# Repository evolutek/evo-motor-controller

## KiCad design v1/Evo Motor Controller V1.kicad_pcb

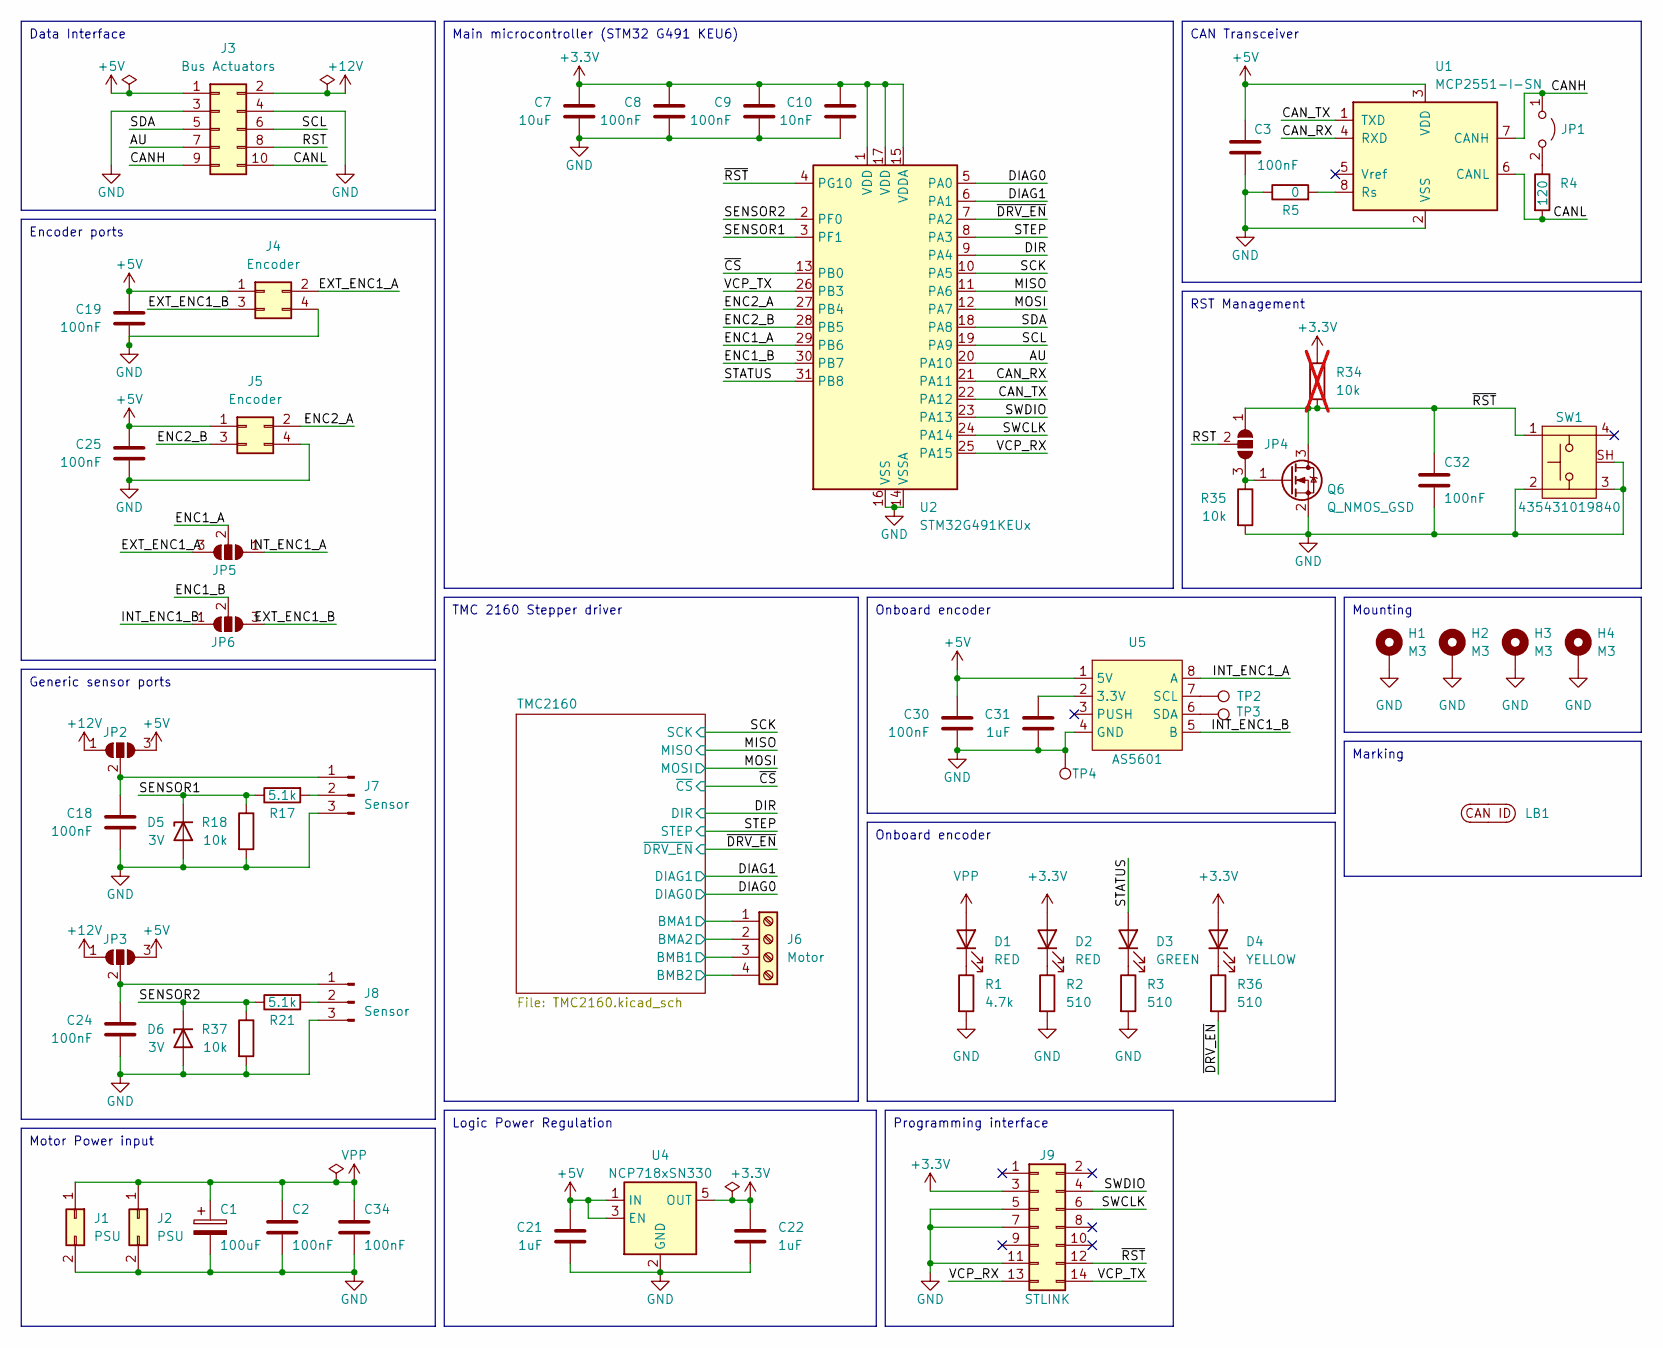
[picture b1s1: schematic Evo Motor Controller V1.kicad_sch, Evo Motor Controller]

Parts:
C1: 100uF; CP_Elec_6.3x7.7
C2, C3, C8, C9, C18, C19, C24, C25, C30, C32, C34: 100nF; C_0603_1608Metric
C7: 10uF; C_0603_1608Metric
C10: 10nF; C_0603_1608Metric
C21, C22, C31: 1uF; C_0603_1608Metric
D1, D2: RED; LED_0805_2012Metric
D3: GREEN; LED_0805_2012Metric
D4: YELLOW; LED_0805_2012Metric
D5, D6: 3V; D_SOD-523
H1, H2, H3, H4: M3; MountingHole_3.2mm_M3_Pad_Via
J1, J2: PSU; 66200221022
J3: Bus Actuators; 690367281076
J4, J5: Encoder; B04B-PASK
J6: Motor; PhoenixContact_MC_1,5_4-G-3.5_1x04_P3.50mm_Horizontal
J7, J8: Sensor; B03B-PASK
J9: STLINK; 62701420621
JP1: Jumper_2_Open; SolderJumper-2_P1.3mm_Open_RoundedPad1.0x1.5mm
JP2, JP3, JP4, JP5, JP6: SolderJumper_3_Open; SolderJumper-3_P1.3mm_Open_RoundedPad1.0x1.5mm
LB1: CAN ID Label 2
Q6: Q_NMOS_GSD; SOT-23
R1: 4.7k; R_0603_1608Metric
R2, R3, R36: 510; R_0603_1608Metric
R4: 120; R_0603_1608Metric
R5: 0; R_0603_1608Metric
R17, R21: 5.1k; R_0603_1608Metric
R18, R35, R37: 10k; R_0603_1608Metric
R34: 10k; R_0603_1608Metric; not fitted
SW1: 435431019840
TP2, TP3, TP4: TestPoint; TestPoint_Pad_D1.0mm
U1: MCP2551-I-SN; SOIC-8_3.9x4.9mm_P1.27mm
U2: STM32G491KEUx; QFN-32-1EP_5x5mm_P0.5mm_EP3.45x3.45mm-Without thermal pad
U4: NCP718xSN330; SOT-23-5
U5: AS5601; SOIC-8_3.9x4.9mm_P1.27mm

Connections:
+3.3V: C7.1, C8.1, C9.1, C10.1, C22.1, D2.2 (A), D4.2 (A), J9.3, R34.1, U2.1 (VDD), U2.15 (VDDA), U2.17 (VDD), U4.5 (OUT); also elsewhere on the board
+5V: C3.1, C19.1, C21.1, C25.1, C30.1, J3.1, J4.1, J5.1, JP2.3 (B), JP3.3 (B), U1.3 (VDD), U4.1 (IN), U4.3 (EN), U5.1 (5V)
+12V: J3.2, JP2.1 (A), JP3.1 (A); also elsewhere on the board
/AU: J3.7, U2.20 (PA10)
/CANH: J3.9, JP1.1 (A), U1.7 (CANH)
/CANL: J3.10, R4.2, U1.6 (CANL)
/CAN_RX: U1.4 (RXD), U2.21 (PA11)
/CAN_TX: U1.1 (TXD), U2.22 (PA12)
/DIAG0: U2.5 (PA0); also elsewhere on the board
/DIAG1: U2.6 (PA1); also elsewhere on the board
/DIR: U2.9 (PA4); also elsewhere on the board
/ENC1_A: JP5.2 (C), U2.29 (PB6)
/ENC1_B: JP6.2 (C), U2.30 (PB7)
/ENC2_A: J5.2, U2.27 (PB4)
/ENC2_B: J5.3, U2.28 (PB5)
/EXT_ENC1_A: J4.2, JP5.3 (B)
/EXT_ENC1_B: J4.3, JP6.3 (B)
/INT_ENC1_A: JP5.1 (A), U5.8 (A)
/INT_ENC1_B: JP6.1 (A), U5.5 (B)
/MISO: U2.11 (PA6); also elsewhere on the board
/MOSI: U2.12 (PA7); also elsewhere on the board
/RST: J3.8, JP4.2 (C)
/SCK: U2.10 (PA5); also elsewhere on the board
/SCL: J3.6, U2.19 (PA9)
/SDA: J3.5, U2.18 (PA8)
/SENSOR1: D5.1 (K), R17.1, R18.1, U2.3 (PF1)
/SENSOR2: D6.1 (K), R21.1, R37.1, U2.2 (PF0)
/STATUS: D3.2 (A), U2.31 (PB8)
/STEP: U2.8 (PA3); also elsewhere on the board
/SWCLK: J9.6, U2.24 (PA14)
/SWDIO: J9.4, U2.23 (PA13)
/TMC2160/BMA1: J6.1; also elsewhere on the board
/TMC2160/BMA2: J6.2; also elsewhere on the board
/TMC2160/BMB1: J6.3; also elsewhere on the board
/TMC2160/BMB2: J6.4; also elsewhere on the board
/VCP_RX: J9.13, U2.25 (PA15)
/VCP_TX: J9.14, U2.26 (PB3)
/~CS: U2.13 (PB0); also elsewhere on the board
/~DRV_EN: R36.2, U2.7 (PA2); also elsewhere on the board
/~RST: C32.1, J9.12, JP4.1 (A), Q6.3 (D), R34.2, SW1.1, U2.4 (PG10)
GND: C1.2, C2.2, C3.2, C7.2, C8.2, C9.2, C10.2, C18.2, C19.2, C21.2, C22.2, C24.2, C25.2, C30.2, C31.2, C32.2, C34.2, D5.2 (A), D6.2 (A), H1.1, H2.1, H3.1, H4.1, J1.2, J2.2, J3.3, J3.4, J4.4, J5.4, J7.3, J8.3, J9.5, J9.7, J9.11, Q6.2 (S), R1.2, R2.2, R3.2, R5.1, R18.2, R35.2, R37.2, SW1.2, SW1.3, SW1.SH, TP4.1, U1.2 (VSS), U2.14 (VSSA), U2.16 (VSS), U2.32 (VSS), U4.2 (GND), U5.4 (GND); also elsewhere on the board
unnamed: D1.1 (K), R1.1
unnamed: D2.1 (K), R2.1
unnamed: D3.1 (K), R3.1
unnamed: D4.1 (K), R36.1
unnamed: C18.1, J7.1, JP2.2 (C)
unnamed: J7.2, R17.2
unnamed: C24.1, J8.1, JP3.2 (C)
unnamed: J8.2, R21.2
unnamed: JP1.2 (B), R4.1
unnamed: JP4.3 (B), Q6.1 (G), R35.1
unnamed: R5.2, U1.8 (Rs)
unnamed: C31.1, U5.2 (3.3V)
unnamed: TP2.1, U5.7 (SCL)
unnamed: TP3.1, U5.6 (SDA)
VPP: C1.1, C2.1, C34.1, D1.2 (A), J1.1, J2.1; also elsewhere on the board

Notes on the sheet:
Marking
Motor Power input
Onboard encoder
Generic sensor ports
Programming interface
Mounting
Data Interface
Encoder ports
TMC 2160 Stepper driver
CAN Transceiver
Logic Power Regulation
Main microcontroller (STM32 G491 KEU6)
RST Management

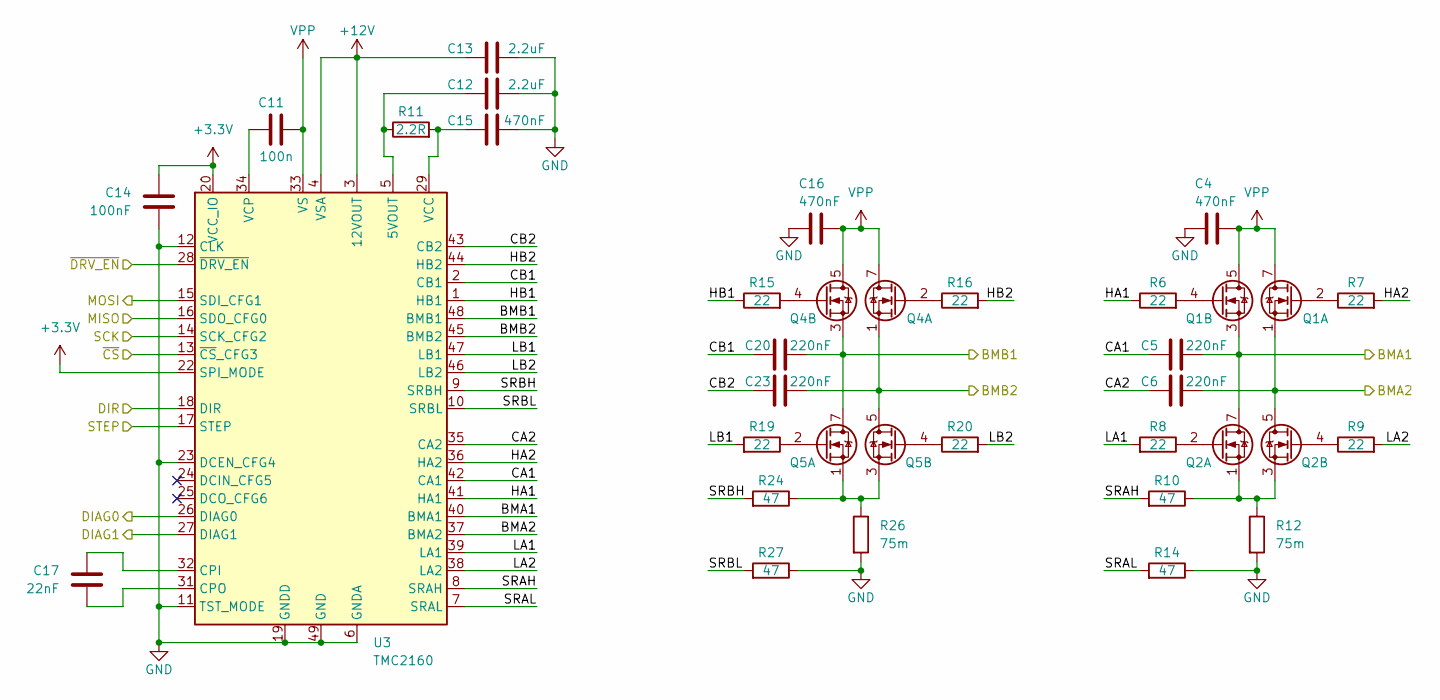
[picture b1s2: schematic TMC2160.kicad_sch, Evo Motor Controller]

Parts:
C4, C15, C16: 470nF; C_0603_1608Metric
C5, C6, C20, C23: 220nF; C_0603_1608Metric
C11: 100n; C_0603_1608Metric
C12, C13: 2.2uF; C_0603_1608Metric
C14: 100nF; C_0603_1608Metric
C17: 22nF; C_0603_1608Metric
Q1, Q2, Q4, Q5: Si9634DY; SO-8_3.9x4.9mm_P1.27mm
R6, R7, R8, R9, R15, R16, R19, R20: 22; R_0603_1608Metric
R10, R14, R24, R27: 47; R_0603_1608Metric
R11: 2.2R; R_0603_1608Metric
R12, R26: 75m; R_1206_3216Metric
U3: TMC2160; TQFP-48-1EP_7x7mm_P0.5mm_EP5x5mm

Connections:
+3.3V: C14.1, U3.20 (VCC_IO), U3.21 (VCC_IO), U3.22 (SPI_MODE); also elsewhere on the board
+12V: C13.1, U3.3 (12VOUT), U3.4 (VSA); also elsewhere on the board
/DIAG0: U3.26 (DIAG0); also elsewhere on the board
/DIAG1: U3.27 (DIAG1); also elsewhere on the board
/DIR: U3.18 (DIR); also elsewhere on the board
/MISO: U3.16 (SDO_CFG0); also elsewhere on the board
/MOSI: U3.15 (SDI_CFG1); also elsewhere on the board
/SCK: U3.14 (SCK_CFG2); also elsewhere on the board
/STEP: U3.17 (STEP); also elsewhere on the board
/TMC2160/BMA1: C5.1, Q1.3 (S), Q2.7 (D), Q2.8 (D), U3.40 (BMA1); also elsewhere on the board
/TMC2160/BMA2: C6.1, Q1.1 (S), Q2.5 (D), Q2.6 (D), U3.37 (BMA2); also elsewhere on the board
/TMC2160/BMB1: C20.1, Q4.3 (S), Q5.7 (D), Q5.8 (D), U3.48 (BMB1); also elsewhere on the board
/TMC2160/BMB2: C23.1, Q4.1 (S), Q5.5 (D), Q5.6 (D), U3.45 (BMB2); also elsewhere on the board
/TMC2160/CA1: C5.2, U3.42 (CA1)
/TMC2160/CA2: C6.2, U3.35 (CA2)
/TMC2160/CB1: C20.2, U3.2 (CB1)
/TMC2160/CB2: C23.2, U3.43 (CB2)
/TMC2160/HA1: R6.1, U3.41 (HA1)
/TMC2160/HA2: R7.2, U3.36 (HA2)
/TMC2160/HB1: R15.1, U3.1 (HB1)
/TMC2160/HB2: R16.2, U3.44 (HB2)
/TMC2160/LA1: R8.2, U3.39 (LA1)
/TMC2160/LA2: R9.2, U3.38 (LA2)
/TMC2160/LB1: R19.2, U3.47 (LB1)
/TMC2160/LB2: R20.2, U3.46 (LB2)
/TMC2160/SRAH: R10.2, U3.8 (SRAH)
/TMC2160/SRAL: R14.2, U3.7 (SRAL)
/TMC2160/SRBH: R24.2, U3.9 (SRBH)
/TMC2160/SRBL: R27.2, U3.10 (SRBL)
/~CS: U3.13 (~CS_CFG3); also elsewhere on the board
/~DRV_EN: U3.28 (~DRV_EN); also elsewhere on the board
GND: C4.2, C12.2, C13.2, C14.2, C15.2, C16.2, R12.2, R14.1, R26.2, R27.1, U3.6 (GNDA), U3.11 (TST_MODE), U3.12 (CLK), U3.19 (GNDD), U3.23 (DCEN_CFG4), U3.30 (GNDD), U3.49 (GND); also elsewhere on the board
unnamed: Q1.2 (G), R7.1
unnamed: Q1.4 (G), R6.2
unnamed: Q2.2 (G), R8.1
unnamed: Q2.1 (S), Q2.3 (S), R10.1, R12.1
unnamed: Q2.4 (G), R9.1
unnamed: Q4.2 (G), R16.1
unnamed: Q4.4 (G), R15.2
unnamed: Q5.2 (G), R19.1
unnamed: Q5.1 (S), Q5.3 (S), R24.1, R26.1
unnamed: Q5.4 (G), R20.1
unnamed: C12.1, R11.1, U3.5 (5VOUT)
unnamed: C17.1, U3.32 (CPI)
unnamed: C17.2, U3.31 (CPO)
unnamed: C15.1, R11.2, U3.29 (VCC)
unnamed: C11.1, U3.34 (VCP)
VPP: C4.1, C11.2, C16.1, Q1.5 (D), Q1.6 (D), Q1.7 (D), Q1.8 (D), Q4.5 (D), Q4.6 (D), Q4.7 (D), Q4.8 (D), U3.33 (VS); also elsewhere on the board

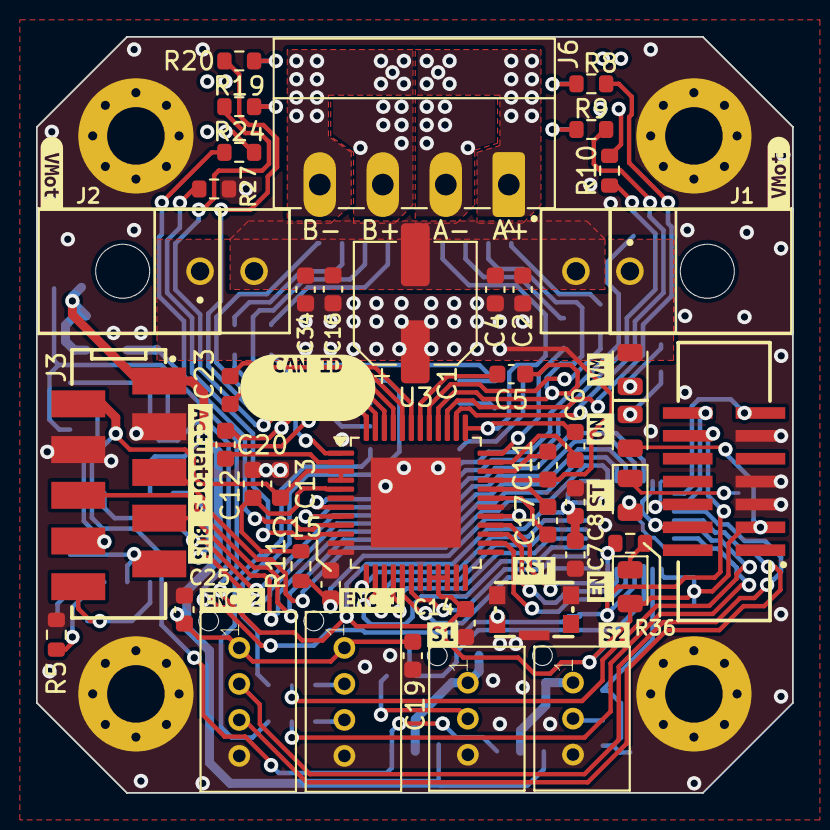
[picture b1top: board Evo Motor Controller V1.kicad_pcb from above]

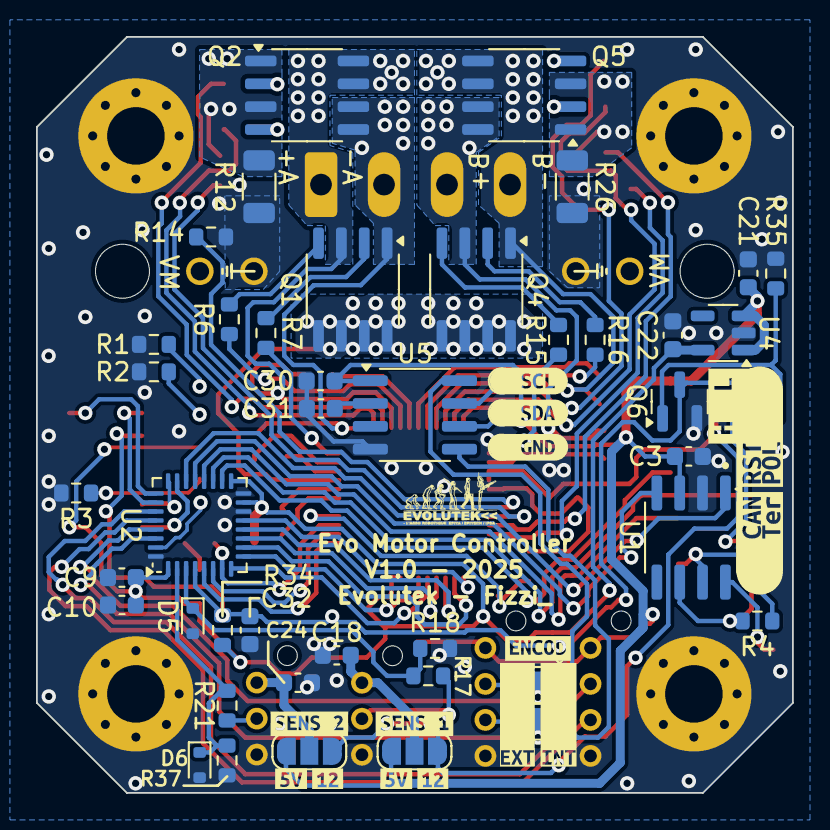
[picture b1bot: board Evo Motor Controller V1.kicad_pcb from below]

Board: 2 copper layers, 42.0 x 42.0 mm, 123 parts (62 on the bottom side), 87 nets.

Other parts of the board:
kibuzzard-676B4A85: G***; kibuzzard-676B4A85
kibuzzard-676B4AC4: G***; kibuzzard-676B4AC4
kibuzzard-676B4BE4: G***; kibuzzard-676B4BE4
kibuzzard-676B4093: G***; kibuzzard-676B4093
kibuzzard-676F6C1C: G***; kibuzzard-676F6C1C
kibuzzard-676F6C2F: G***; kibuzzard-676F6C2F
kibuzzard-67856E2C: G***; kibuzzard-67856E2C
kibuzzard-67856E49: G***; kibuzzard-67856E49
kibuzzard-67856FF7, kibuzzard-67856FF7#2: G***; kibuzzard-67856FF7
kibuzzard-678570A8: G***; kibuzzard-678570A8
kibuzzard-678570B0: G***; kibuzzard-678570B0
kibuzzard-678570B4: G***; kibuzzard-678570B4
kibuzzard-678572E9: G***; kibuzzard-678572E9
kibuzzard-6786847E: G***; kibuzzard-6786847E
kibuzzard-6786849F: G***; kibuzzard-6786849F
kibuzzard-6786851A: G***; kibuzzard-6786851A
kibuzzard-67857003, kibuzzard-67857003#2: G***; kibuzzard-67857003
kibuzzard-67857028: G***; kibuzzard-67857028
kibuzzard-67857113: G***; kibuzzard-67857113
kibuzzard-67857122: G***; kibuzzard-67857122
kibuzzard-67857138: G***; kibuzzard-67857138
kibuzzard-67857263: G***; kibuzzard-67857263
kibuzzard-67857283: G***; kibuzzard-67857283
kibuzzard-67868504: G***; kibuzzard-67868504
kibuzzard-67868567: G***; kibuzzard-67868567

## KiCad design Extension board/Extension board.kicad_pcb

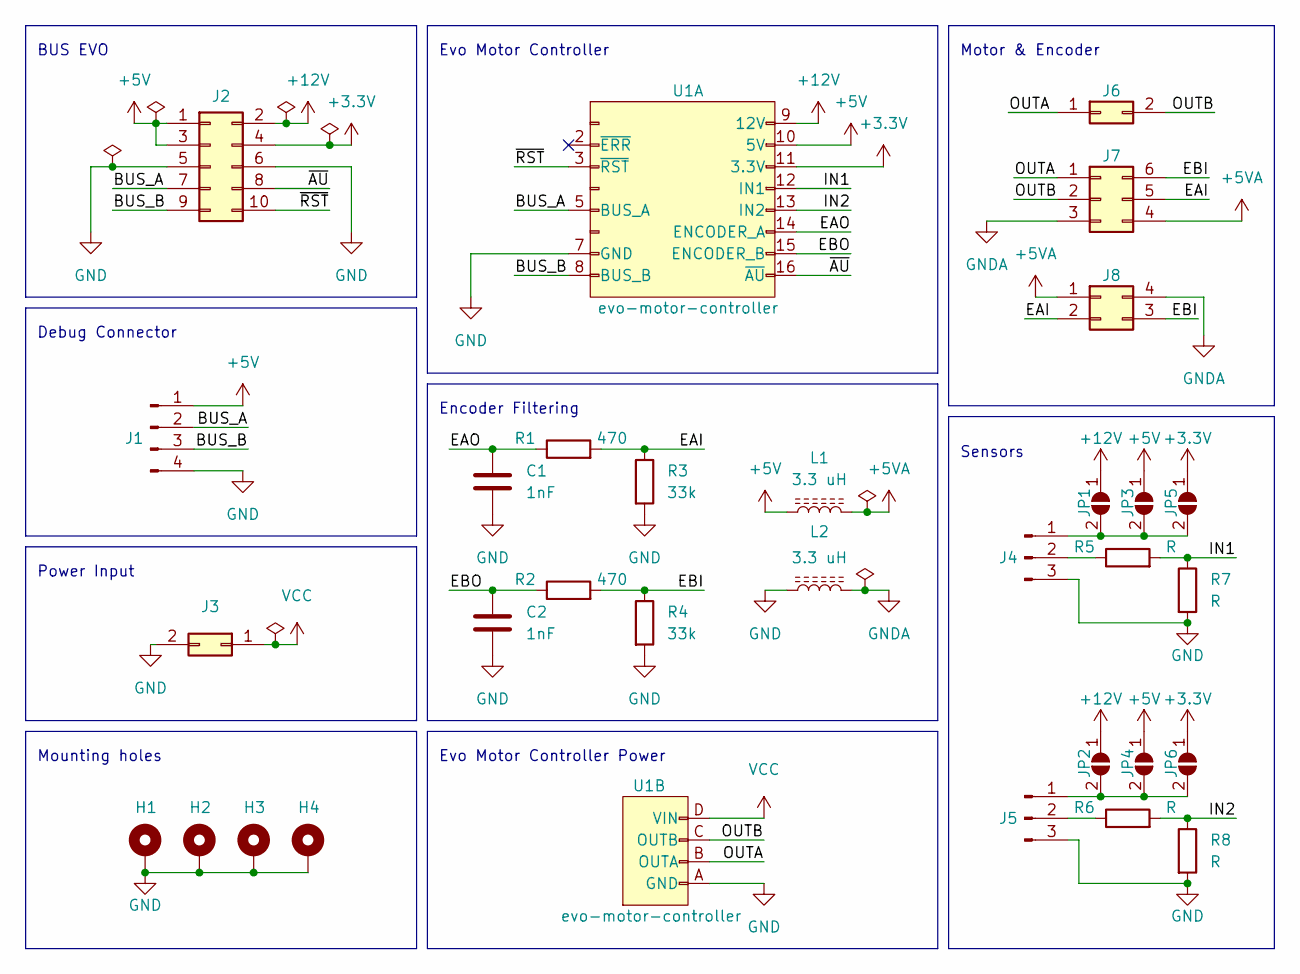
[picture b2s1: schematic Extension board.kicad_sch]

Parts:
C1, C2: 1nF; C_0603_1608Metric
H1, H2, H3, H4: MountingHole_Pad; MountingHole_3.2mm_M3_Pad_Via
J1: Conn_01x04_Male; B04B-PASK
J2: Conn_02x05_Odd_Even; 690367281076
J3, J6: Conn_02x01; 649002227222
J4, J5: Conn_01x03_Male; B03B-PASK
J7: Conn_02x03_Counter_Clockwise; 66200621022
J8: Conn_02x02_Counter_Clockwise; 66200421022
JP1, JP2, JP3, JP4, JP5, JP6: SolderJumper_2_Open; SolderJumper-2_P1.3mm_Open_TrianglePad1.0x1.5mm
L1, L2: 3.3 uH; L_0603_1608Metric
R1, R2: 470; R_0603_1608Metric
R3, R4: 33k; R_0603_1608Metric
R5, R6, R7, R8: R; R_0603_1608Metric
U1: evo-motor-controller

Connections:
+3.3V: J2.4, JP5.1 (A), JP6.1 (A), U1.11 (3.3V)
+5V: J1.1, J2.1, J2.3, JP3.1 (A), JP4.1 (A), L1.1, U1.10 (5V)
+5VA: J7.4, J8.1, L1.2
+12V: J2.2, JP1.1 (A), JP2.1 (A), U1.9 (12V)
/BUS_A: J1.2, J2.7, U1.5 (BUS_A)
/BUS_B: J1.3, J2.9, U1.8 (BUS_B)
/EAI: J7.5, J8.2, R1.2, R3.1
/EAO: C1.1, R1.1, U1.14 (ENCODER_A)
/EBI: J7.6, J8.3, R2.2, R4.1
/EBO: C2.1, R2.1, U1.15 (ENCODER_B)
/IN1: R5.2, R7.1, U1.12 (IN1)
/IN2: R6.2, R8.1, U1.13 (IN2)
/OUTA: J6.1, J7.1, U1.B (OUTA)
/OUTB: J6.2, J7.2, U1.C (OUTB)
/~AU: J2.8, U1.16 (~AU)
/~RST: J2.10, U1.3 (~RST)
GND: C1.2, C2.2, H1.1, H2.1, H3.1, H4.1, J1.4, J2.5, J2.6, J3.2, J4.3, J5.3, L2.1, R3.2, R4.2, R7.2, R8.2, U1.7 (GND), U1.A (GND)
GNDA: J7.3, J8.4, L2.2
unnamed: J4.1, JP1.2 (B), JP3.2 (B), JP5.2 (B)
unnamed: J4.2, R5.1
unnamed: J5.1, JP2.2 (B), JP4.2 (B), JP6.2 (B)
unnamed: J5.2, R6.1
VCC: J3.1, U1.D (VIN)

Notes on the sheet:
Evo Motor Controller
Encoder Filtering
Evo Motor Controller Power
Power Input
Motor & Encoder
Mounting holes
BUS EVO
Debug Connector
Sensors

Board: 2 copper layers, 31 parts (0 on the bottom side), 23 nets, no tracks yet.

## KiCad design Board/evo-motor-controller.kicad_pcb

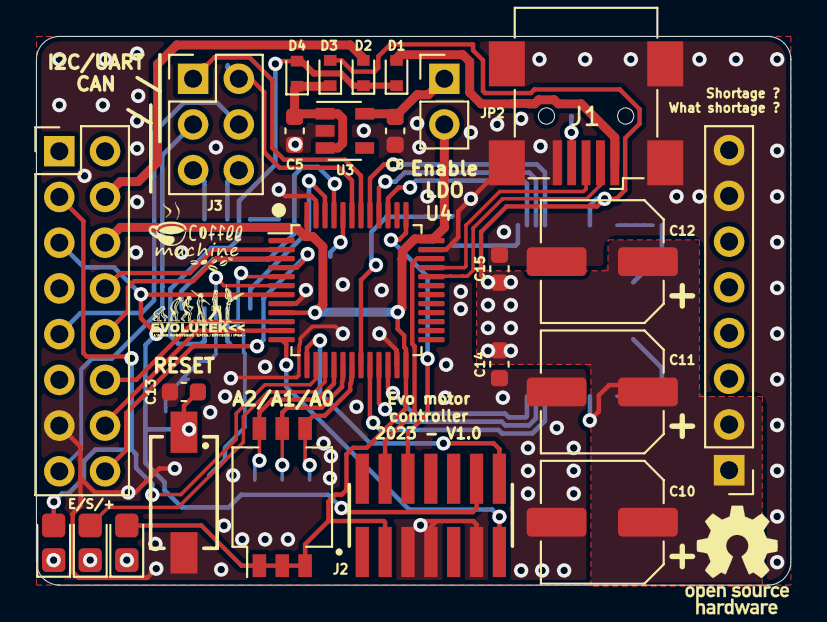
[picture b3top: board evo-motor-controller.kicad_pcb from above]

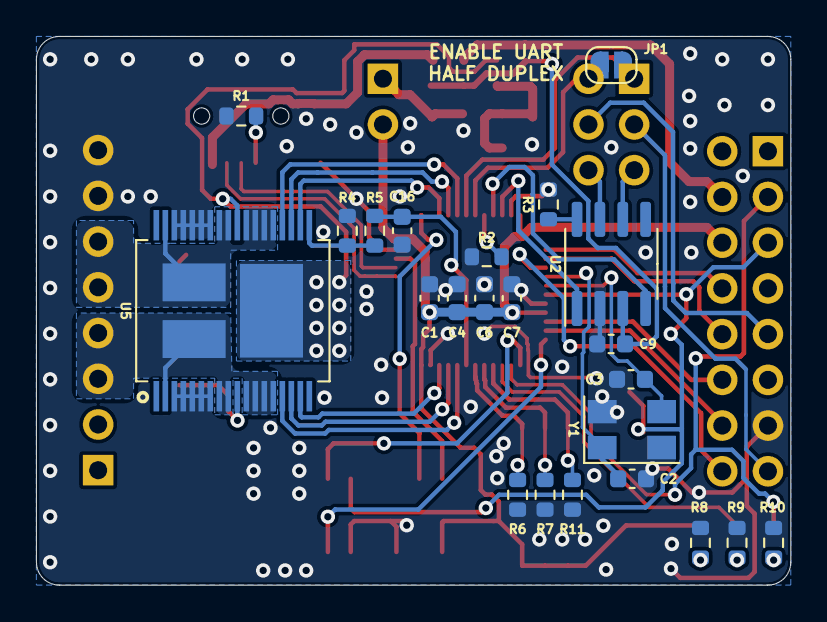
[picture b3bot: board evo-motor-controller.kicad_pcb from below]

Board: 2 copper layers, 41.9 x 30.5 mm, 47 parts (23 on the bottom side), 51 nets.

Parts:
C1, C14: 10uF; C_0603_1608Metric
C2, C3: 18pF; C_0603_1608Metric
C4, C6, C9, C13, C15: 100nF; C_0603_1608Metric
C5, C8: 1uF; C_0603_1608Metric
C7: 10nF; C_0603_1608Metric
C10, C11, C12: 100uF; C_Elec_6.3x7.7
C16: 33nF; C_0603_1608Metric
D1, D2, D3, D4: D; D_SOD-523
D5, D7: RED; LED_0805_2012Metric_Castellated
D6: YELLOW; LED_0805_2012Metric_Castellated
J1: USB_B_Mini; USB_Mini-B_Wuerth_65100516121_Horizontal
J2: FTSH-107-01-L-DV-K; SAMTEC_FTSH-107-01-L-DV-K
J3: Conn_02x03_Odd_Even; PinHeader_2x03_P2.54mm_Vertical
JP1: Jumper_NO_Small; SolderJumper-2_P1.3mm_Open_RoundedPad1.0x1.5mm
JP2: Jumper_NO_Small; PinHeader_1x02_P2.54mm_Vertical
R1: 100K; R_0603_1608Metric
R2, R3, R6, R7, R11: 10K; R_0603_1608Metric
R4, R5, R8, R9, R10: 1K; R_0603_1608Metric
SW1: SW_Push; 434121043836
SW2: SW_DIP_x03; SW_DIP_SPSTx03_Slide_KingTek_DSHP03TS_W7.62mm_P1.27mm
U1: G2-Port_extended; G2-port-extended
U2: MCP2551-I-SN; SOIC-8_3.9x4.9mm_P1.27mm
U3: NCP718xSN330; SOT-23-5
U4: STM32F103C8Tx; LQFP-48_7x7mm_P0.5mm
U5: VNH7040AYTR
Y1: 16 MHz; Crystal_SMD_5032-4Pin_5.0x3.2mm

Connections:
+3V3: C1.1, C4.1, C6.1, C7.1, D5.2, J2.3, JP2.2, SW2.1, SW2.2, SW2.3, U1.11, U4.9, U4.24, U4.36, U4.48
+5V: C9.1, D1.1, D2.1, D4.2, U2.3
/A0: R6.1, SW2.4, U4.18
/A1: R7.1, SW2.5, U4.17
/A2: R11.1, SW2.6, U4.16
/BUS_A: J3.4, U1.5
/BUS_B: J3.3, U1.8
/CANH: J3.6, U2.7
/CANL: J3.5, U2.6
/CAN_RX: U2.4, U4.45
/CAN_TX: U2.1, U4.46
/ENCODER_A: U1.14, U4.10
/ENCODER_B: U1.15, U4.11
/ERR_MOTOR: D7.2, U1.2, U4.14
/IN1: U1.12, U4.2
/IN2: U1.13, U4.3
/INA: U4.21, U5.3
/INB: U4.40, U5.4
/LED_STATUS: D6.2, U4.15
/MS: C16.1, R5.1, U4.19
/MS_EN: U4.39, U5.8
/OUTA: U1.C, U5.11
/OUTB: U1.B, U5.12
/PWM: U4.22, U5.5
/SCL-TX: J3.1, JP1.1, U4.42
/SDA-RX: J3.2, JP1.2, U4.43
/SEL0: U4.20, U5.6
/SEL1: U4.41, U5.7
/SWCLK: J2.6, U4.37
/SWDIO: J2.4, U4.34
/USB+: J1.3, U4.33
/USB-: J1.2, U4.32
/VCP_RX: J2.14, U4.13
/VCP_TX: J2.13, U4.12
/~AU: U1.16, U4.4
/~RST: C13.1, J2.12, SW1.1, U1.3, U4.7
GND: C1.2, C2.1, C3.1, C4.2, C5.2, C6.2, C7.2, C8.2, C9.2, C10.2, C11.2, C12.2, C13.2, C14.2, C15.2, C16.2, J1.5, J1.6, J2.5, J2.7, J2.11, R1.1, R2.1, R3.2, R4.2, R6.2, R7.2, R8.2, R9.2, R10.2, R11.2, SW1.2, U1.7, U1.A, U2.2, U3.2, U4.8, U4.23, U4.35, U4.47, U5.2, Y1.2, Y1.4
unnamed: C2.2, U4.5, Y1.1
unnamed: C3.2, U4.6, Y1.3
unnamed: C5.1, D3.1, D4.1, U3.1, U3.3
unnamed: C8.1, JP2.1, U3.5
unnamed: D1.2, J1.1
unnamed: D2.2, U1.10
unnamed: D5.1, R8.1
unnamed: D6.1, R9.1
unnamed: D7.1, R10.1
unnamed: J1.4, R1.2
unnamed: R2.2, U4.44
unnamed: R3.1, U2.8
unnamed: R4.1, R5.2, U5.9
VCC: C10.1, C11.1, C12.1, C14.1, C15.1, D3.2, U1.D, U5.1

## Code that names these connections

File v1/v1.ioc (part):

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Mcu.Name=STM32G491K(C-E)Ux
Mcu.Package=UFQFPN32
Mcu.UserName=STM32G491KEUx
PA0.GPIOParameters=GPIO_Label
PA0.GPIO_Label=DIAG0
PA0.Signal=GPXTI0
PA1.GPIOParameters=GPIO_Label
PA1.GPIO_Label=DIAG1
PA1.Signal=GPXTI1
PA10.GPIOParameters=GPIO_Label
PA10.GPIO_Label=AU
PA10.Signal=GPIO_Output
PA11.GPIOParameters=GPIO_Label
PA11.GPIO_Label=CAN_RX
PA11.Mode=FDCAN_Activate
PA11.Signal=FDCAN1_RX
PA12.GPIOParameters=GPIO_Label
PA12.GPIO_Label=CAN_TX
PA12.Mode=FDCAN_Activate
PA12.Signal=FDCAN1_TX
PA13.GPIOParameters=GPIO_Label
PA13.GPIO_Label=SWDIO
PA13.Mode=Serial_Wire
PA13.Signal=SYS_JTMS-SWDIO
PA14.GPIOParameters=GPIO_Label
PA14.GPIO_Label=SWCLK
PA14.Mode=Serial_Wire
PA14.Signal=SYS_JTCK-SWCLK
PA15.GPIOParameters=GPIO_Label
PA15.GPIO_Label=VCP_RX
PA15.Mode=Asynchronous
PA15.Signal=USART2_RX
PA2.GPIOParameters=GPIO_Label
PA2.GPIO_Label=N_EN
PA2.Signal=GPIO_Output
PA3.GPIOParameters=GPIO_Label
PA3.GPIO_Label=STEP
PA3.Signal=S_TIM2_CH4
PA4.GPIOParameters=GPIO_Label
PA4.GPIO_Label=DIR
PA4.Signal=GPIO_Output
PA5.GPIOParameters=GPIO_Label
PA5.GPIO_Label=SCK
PA5.Mode=Full_Duplex_Master
PA5.Signal=SPI1_SCK
PA6.GPIOParameters=GPIO_Label
PA6.GPIO_Label=MISO
PA6.Mode=Full_Duplex_Master
PA6.Signal=SPI1_MISO
PA7.GPIOParameters=GPIO_Label
PA7.GPIO_Label=MOSI
PA7.Mode=Full_Duplex_Master
PA7.Signal=SPI1_MOSI
PA8.GPIOParameters=GPIO_Label
PA8.GPIO_Label=SDA
PA8.Mode=I2C
PA8.Signal=I2C2_SDA
PA9.GPIOParameters=GPIO_Label
PA9.GPIO_Label=SCL
PA9.Mode=I2C
PA9.Signal=I2C2_SCL
PB0.GPIOParameters=GPIO_Label
PB0.GPIO_Label=N_CS
PB0.Signal=GPIO_Output
PB3.GPIOParameters=GPIO_Label
PB3.GPIO_Label=VCP_TX
PB3.Mode=Asynchronous
PB3.Signal=USART2_TX
PB4.GPIOParameters=GPIO_Label
PB4.GPIO_Label=ENC2_A
PB4.Signal=S_TIM3_CH1
PB5.GPIOParameters=GPIO_Label
PB5.GPIO_Label=ENC2_B
PB5.Signal=S_TIM3_CH2
PB6.GPIOParameters=GPIO_Label
PB6.GPIO_Label=ENC1_A
PB6.Signal=S_TIM4_CH1
PB7.GPIOParameters=GPIO_Label
PB7.GPIO_Label=ENC1_B
PB7.Signal=S_TIM4_CH2
PB8-BOOT0.GPIOParameters=GPIO_Label
PB8-BOOT0.GPIO_Label=STATUS
PB8-BOOT0.Signal=GPIO_Output
PF0-OSC_IN.GPIOParameters=GPIO_Label
PF0-OSC_IN.GPIO_Label=SENSOR_2
PF0-OSC_IN.Mode=IN10-Single-Ended
PF0-OSC_IN.Signal=ADC1_IN10
PF1-OSC_OUT.GPIOParameters=GPIO_Label
PF1-OSC_OUT.GPIO_Label=SENSOR_1
PF1-OSC_OUT.Mode=IN10-Single-Ended
PF1-OSC_OUT.Signal=ADC2_IN10
RCC.HSE_VALUE=8000000
RCC.SYSCLKFreq_VALUE=16000000
board=custom

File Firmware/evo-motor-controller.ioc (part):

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Mcu.Name=STM32F103C(8-B)Tx
Mcu.Package=LQFP48
Mcu.UserName=STM32F103C8Tx
PA0-WKUP.GPIOParameters=GPIO_Label
PA0-WKUP.GPIO_Label=ENCODER_A
PA0-WKUP.Signal=S_TIM2_CH1_ETR
PA1.GPIOParameters=GPIO_Label
PA1.GPIO_Label=ENCODER_B
PA1.Signal=S_TIM2_CH2
PA11.Mode=Device
PA11.Signal=USB_DM
PA12.Mode=Device
PA12.Signal=USB_DP
PA13.GPIOParameters=GPIO_Label
PA13.GPIO_Label=SWDIO
PA13.Mode=Serial_Wire
PA13.Signal=SYS_JTMS-SWDIO
PA14.GPIOParameters=GPIO_Label
PA14.GPIO_Label=SWCLK
PA14.Mode=Serial_Wire
PA14.Signal=SYS_JTCK-SWCLK
PA2.GPIOParameters=GPIO_Label
PA2.GPIO_Label=VCP_TX
PA2.Mode=Asynchronous
PA2.Signal=USART2_TX
PA3.GPIOParameters=GPIO_Label
PA3.GPIO_Label=VCP_RX
PA3.Mode=Asynchronous
PA3.Signal=USART2_RX
PA4.GPIOParameters=GPIO_Label
PA4.GPIO_Label=ERR_MOTOR
PA4.Signal=GPIO_Output
PA5.GPIOParameters=GPIO_Label
PA5.GPIO_Label=LED_STATUS
PA5.Signal=GPIO_Output
PB6.GPIOParameters=GPIO_Label
PB6.GPIO_Label=SCL
PB6.Mode=I2C
PB6.Signal=I2C1_SCL
PB7.GPIOParameters=GPIO_Label
PB7.GPIO_Label=SDA
PB7.Mode=I2C
PB7.Signal=I2C1_SDA
PB8.Mode=CAN_Activate
PB8.Signal=CAN_RX
PB9.Mode=CAN_Activate
PB9.Signal=CAN_TX
PC13-TAMPER-RTC.GPIOParameters=GPIO_Label
PC13-TAMPER-RTC.GPIO_Label=IN1
PC13-TAMPER-RTC.Signal=GPIO_Input
PC14-OSC32_IN.GPIOParameters=GPIO_Label
PC14-OSC32_IN.GPIO_Label=IN2
PC14-OSC32_IN.Signal=GPIO_Input
PC15-OSC32_OUT.GPIOParameters=GPIO_Label
PC15-OSC32_OUT.GPIO_Label=AU
PC15-OSC32_OUT.Signal=GPIO_Input
PD0-OSC_IN.Mode=HSE-External-Oscillator
PD0-OSC_IN.Signal=RCC_OSC_IN
PD1-OSC_OUT.Mode=HSE-External-Oscillator
PD1-OSC_OUT.Signal=RCC_OSC_OUT
RCC.HSEDivPLL=RCC_HSE_PREDIV_DIV2
RCC.HSE_VALUE=16000000
RCC.SYSCLKFreq_VALUE=72000000
RCC.SYSCLKSource=RCC_SYSCLKSOURCE_PLLCLK
board=custom

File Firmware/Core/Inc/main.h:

/* USER CODE BEGIN Header */
/**
  ******************************************************************************
  * @file           : main.h
  * @brief          : Header for main.c file.
  *                   This file contains the common defines of the application.
  ******************************************************************************
  * @attention
  *
  * <h2><center>&copy; Copyright (c) 2022 STMicroelectronics.
  * All rights reserved.</center></h2>
  *
  * This software component is licensed by ST under BSD 3-Clause license,
  * the "License"; You may not use this file except in compliance with the
  * License. You may obtain a copy of the License at:
  *                        opensource.org/licenses/BSD-3-Clause
  *
  ******************************************************************************
  */
/* USER CODE END Header */

/* Define to prevent recursive inclusion -------------------------------------*/
#ifndef __MAIN_H
#define __MAIN_H

#ifdef __cplusplus
extern "C" {
#endif

/* Includes ------------------------------------------------------------------*/
#include "stm32f1xx_hal.h"

/* Private includes ----------------------------------------------------------*/
/* USER CODE BEGIN Includes */

/* USER CODE END Includes */

/* Exported types ------------------------------------------------------------*/
/* USER CODE BEGIN ET */

/* USER CODE END ET */

/* Exported constants --------------------------------------------------------*/
/* USER CODE BEGIN EC */

/* USER CODE END EC */

/* Exported macro ------------------------------------------------------------*/
/* USER CODE BEGIN EM */

/* USER CODE END EM */

void HAL_TIM_MspPostInit(TIM_HandleTypeDef *htim);

/* Exported functions prototypes ---------------------------------------------*/
void Error_Handler(void);

/* USER CODE BEGIN EFP */

/* USER CODE END EFP */

/* Private defines -----------------------------------------------------------*/
#define LED_STATUS_Pin GPIO_PIN_13
#define LED_STATUS_GPIO_Port GPIOC
#define IN1_Pin GPIO_PIN_14
#define IN1_GPIO_Port GPIOC
#define IN2_Pin GPIO_PIN_15
#define IN2_GPIO_Port GPIOC
#define ENCODER_A_Pin GPIO_PIN_0
#define ENCODER_A_GPIO_Port GPIOA
#define ENCODER_B_Pin GPIO_PIN_1
#define ENCODER_B_GPIO_Port GPIOA
#define VCP_TX_Pin GPIO_PIN_2
#define VCP_TX_GPIO_Port GPIOA
#define VCP_RX_Pin GPIO_PIN_3
#define VCP_RX_GPIO_Port GPIOA
#define SEL1_Pin GPIO_PIN_6
#define SEL1_GPIO_Port GPIOA
#define INB_Pin GPIO_PIN_7
#define INB_GPIO_Port GPIOA
#define MS_ENABLE_Pin GPIO_PIN_0
#define MS_ENABLE_GPIO_Port GPIOB
#define MS_Pin GPIO_PIN_1
#define MS_GPIO_Port GPIOB
#define PWM_Pin GPIO_PIN_8
#define PWM_GPIO_Port GPIOA
#define INA_Pin GPIO_PIN_9
#define INA_GPIO_Port GPIOA
#define SEL0_Pin GPIO_PIN_10
#define SEL0_GPIO_Port GPIOA
#define USB__Pin GPIO_PIN_11
#define USB__GPIO_Port GPIOA
#define USB_A12_Pin GPIO_PIN_12
#define USB_A12_GPIO_Port GPIOA
#define SWDIO_Pin GPIO_PIN_13
#define SWDIO_GPIO_Port GPIOA
#define SWCLK_Pin GPIO_PIN_14
#define SWCLK_GPIO_Port GPIOA
#define SCL_Pin GPIO_PIN_6
#define SCL_GPIO_Port GPIOB
#define SDA_Pin GPIO_PIN_7
#define SDA_GPIO_Port GPIOB
#define AU_Pin GPIO_PIN_8
#define AU_GPIO_Port GPIOB
#define ERR_MOTOR_Pin GPIO_PIN_9
#define ERR_MOTOR_GPIO_Port GPIOB
/* USER CODE BEGIN Private defines */

/* USER CODE END Private defines */

#ifdef __cplusplus
}
#endif

#endif /* __MAIN_H */

/************************ (C) COPYRIGHT STMicroelectronics *****END OF FILE****/

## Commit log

2022-11-27 Add gitignore
2022-11-27 Wip board
2022-11-27 Wip first BOM
2022-12-03 Schematics of V1.0 Done
2022-12-03 Add CubeMX Project
2022-12-05 Minor fixes
2023-01-10 [1.0] Pre-release of the board
2023-01-10 Update firmware project
2023-03-15 Wip Extension board
2023-03-15 Add mounting holes
2024-12-06 Move board to proto-alpha
2024-12-06 Remove useless files
2024-12-18 WIP V1.0
2024-12-27 started routing
2024-12-28 carried on routing
2024-12-29 R1
    FINALLY found a f-ing spot for R1
2024-12-29 carried on routing
    12V sensors
    Top layer heat dissipation
2024-12-29 minor changes
2024-12-30 before review
2024-12-30 after review (WIP)
2025-01-02 cleaned up
2025-01-02 general progress
2025-01-11 cleaned up schematic, done with routing
2025-01-13 waiting for review
    Haven't figured out how to round the corners
2025-01-14 minor touchups before production
2025-01-15 Release V1.0
2025-01-30 initial
